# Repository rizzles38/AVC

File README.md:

# Rover 12

An autonomous 1/10th scale R/C car built by Maria Pikusova and Bob Somers.

## Documentation

### Nodes

* `joint_state_publisher` (joint\_state\_publisher/joint\_state\_publisher):
  Listens on individual joint topics under `/joints` and  publishes a single
  sensor\_msgs/JointState which contains the state of all joints in the robot
  (based on the URDF).
* `robot_state_publisher` (robot\_state\_publisher/state\_publisher): Listens
  to the combined joint states of the robot on `/joint_states`, runs forward
  kinematics based on the URDF, and publishes the results to the TF2 tree.
* `control_board` (rover12\_drivers/control\_board\_node): Driver node which
  talks to the control board. Subscribes to the `/control/autonomous` and
  `/control/command` topics for controlling whether we're in autonomous mode and
  what the velocity/steering command is. Publishes data and status of the wheel
  encoders on the `/wheels/data` and `/wheels/status` topics, as well as the
  status of autonomous mode (from the control board) on `/estop`.
* `sensor_board` (rover12\_drivers/sensor\_board\_node): Publishes data from the
  IMU sensor and GPS sensor, including status information from both sensors
  about their operating modes, current performance, and calibration status.
* `soft_estop` (soft\_estop/soft\_estop): Continuously publishes on the
  `/control/autonomous` topic that requests that the hardware allow the robot to
  be in autonomous mode. Can be run on a computer different than the robot to
  have remote control of autonomous mode. Stands for "software emergency stop".
* `odom_localizer` (robot\_localization/ukf\_localization\_node): Runs an
  unscented Kalman filter over the wheel odometry and IMU data to produce a
  state estimate of `base_link` in the `odom` frame. Subscribes to `/imu/data`
  and `/wheels/data` for sensor inputs and publishes its pose estimate on
  `/odom/filtered`. Also publishes the transform from the `odom` frame to the
  `base_link` frame in the TF2 tree.

### Topics

* `/control`: Namespace for talking to the control board.
  * `/autonomous` (rover12\_drivers/AutonomousMode): Controls whether the
    software wants to be in autonomous mode or not.
  * `/command` (ackermann\_msgs/AckermannDriveStamped): Contains the velocity
    and steering angle command we want the car to execute.
* `/estop` (rover12\_drivers/AutonomousMode): The current state of autonomous
  mode, according to the control board. The firmware makes the final call, based
  on whether the software and physical autonomous mode switch are engaged.
* `/gps`: Namespace for the GPS sensor.
  * `/fix` (sensor\_msgs/NavSatFix): Current GPS position estimate.
  * `/status` (rover12\_drivers/GpsStatus): Extra status information from the
    GPS sensor.
* `/imu`: Namespace for the inertial sensor.
  * `/data` (sensor\_msgs/Imu): Current inertial data and absolute orientation
    estimate from the sensor.
  * `/status` (rover12\_drivers/ImuStatus): Extra status information from the
    IMU, such as its operating mode and calibration state.
* `/joint_states` (sensor\_msgs/JointState): A combined, consistent JointState
  for all joints in the robot, based on the URDF. Published by the
  `joint_state_publisher`.
* `/joints`: Namespace for controlling individual joint states.
  * `/fl_steer` (sensor\_msgs/JointState): Steering rotation of the front left kingpin.
  * `/fr_steer` (sensor\_msgs/JointState): Steering rotation of the front right kingpin.
  * `/fl_wheel` (sensor\_msgs/JointState): Rotation of the front left wheel.
  * `/fr_wheel` (sensor\_msgs/JointState): Rotation of the front right wheel.
  * `/rl_wheel` (sensor\_msgs/JointState): Rotation of the rear left wheel.
  * `/rr_wheel` (sensor\_msgs/JointState): Rotation of the rear right wheel.
* `/odom`: Namespace for pose information in the odom frame.
  * `/filtered` (nav\_msgs/Odometry): Output pose estimate from the UKF in the
    `odom` frame.
* `/wheels`: Namespace for the quadrature wheel encoders.
  * `/data` (geometry\_msgs/TwistWithCovarianceStamped): Instantaneous forward
    speed based on averaging wheel speeds from the quadrature wheel encoders.
  * `/status` (rover12\_drivers/EncoderStatus): Extra status data from the
    wheel encoders (such as raw tick counts).

### TF2 Frames
* `odom`: World-fixed frame in which `base_link` moves smoothly over the short
  term, but accumulates drift error over the long term. The origin of this frame
  is the startup location of the robot.
  * `base_link`: Fixed to robot, parent of all other frames attached to the
    robot. Origin is at the rear axle (X forward, Y out the driver's side, Z
    up).
    * `imu`: Origin at the sensing center of the IMU, oriented according to the
      IMUs local coordinate frame.
    * `gps`: Origen at the sensing center of the GPS antenna, oriented in the
      same direction as `base_link`.
    * `body`: Origin at the approximate center of mass of the body shell,
      primarily used for drawing the robot model at a sensible location in rviz.
    * `rl_wheel`: Origin in the center of the rear left wheel. Rotates about
      its Y axis as the wheel rotates. Located half the track distance from
      `base_link` along its Y axis.
    * `rr_wheel`: Origin in the center of the rear right wheel. Rotates about
      its Y axis as the wheel rotates. Located half the track distance from
      `base_link` along its Y axis.
    * `f_axle`: Origin in the center of the front axle, oriented in the same
      way as `base_link`. The distance between this frame and `base_link` is the
      wheelbase distance along their colinear X axes.
      * `fl_kingpin`: Origin in the steering center of the front left wheel,
        located half the track distance from `f_axle` along its Y axis. Rotates
        about its Z axis.
        * `fl_wheel`: Origin in the center of the front left wheel, orientation
          accounting for the rotation of `fl_kingpin`. Rotates about its Y axis
          as the wheel rotates.
      * `fr_kingpin`: Origin in the steering center of the front right wheel,
        located half the track distance from `f_axle` along its Y axis. Rotates
        about its Z axis.
        * `fr_wheel`: Origin in the center of the front right wheel, orientation
          accounting for the rotation of `fr_kingpin`. Rotates about its Y axis
          as the wheel rotates.

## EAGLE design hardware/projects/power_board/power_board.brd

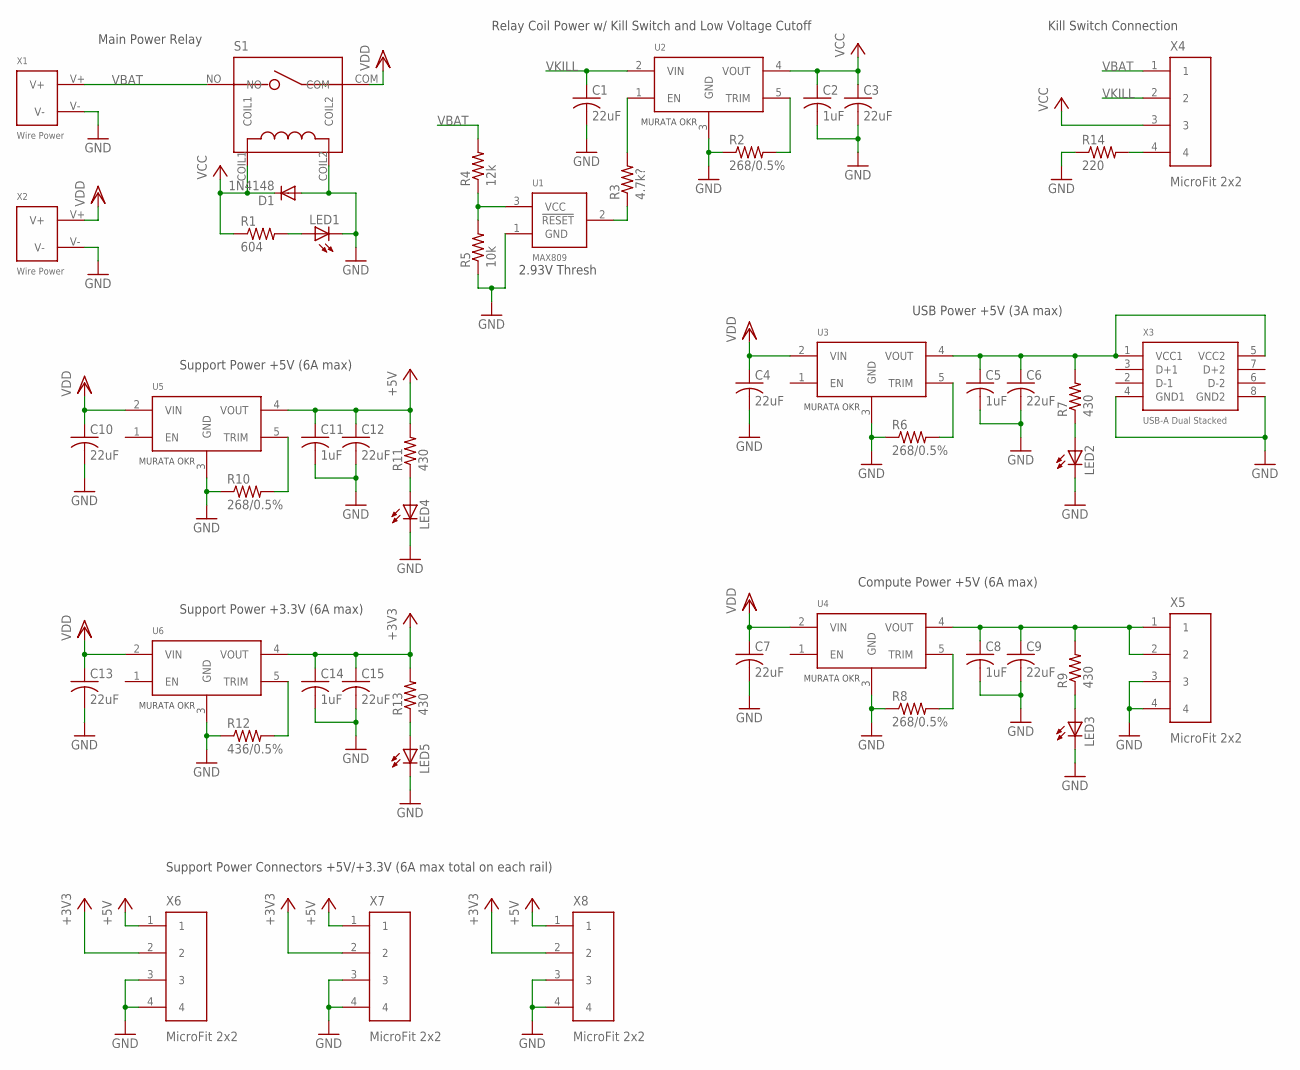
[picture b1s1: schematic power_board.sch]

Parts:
C1, C3, C4, C6, C7, C9, C10, C12, C13, C15: 22uF; C1210
C2, C5, C8, C11, C14: 1uF; C1210
D1: 1N4148; SOD123
LED1, LED2, LED3, LED4, LED5: LEDCHIPLED_0603; CHIPLED_0603
R1: 604; R0603
R2, R6, R8, R10: 268/0.5%; R0603
R3: 4.7k?; R0603
R4: 12k; R0603
R5: 10k; R0603
R7, R9, R11, R13: 430; R0603
R12: 436/0.5%; R0603
R14: 220; R0603
S1: T90S1D12-5
U1: MAX809; SOT-23
U2, U3, U4, U5, U6: MURATA-OKR
X1, X2: WIRE-POWER
X3: USB-A-STACKED
X4, X5, X6, X7, X8: MICROFIT-2X2-SMD; MICROFIT-2X2-0430450411

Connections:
+3V3: C14.1, C15.1, R13.2, U6.4 (VOUT), X6.2, X7.2, X8.2
+5V: C11.1, C12.1, R11.2, U5.4 (VOUT), X6.1, X7.1, X8.1
GND: C1.2, C2.2, C3.2, C4.2, C5.2, C6.2, C7.2, C8.2, C9.2, C10.2, C11.2, C12.2, C13.2, C14.2, C15.2, D1.A, LED1.C, LED2.C, LED3.C, LED4.C, LED5.C, R2.1, R5.1, R6.1, R8.1, R10.1, R12.1, R14.1, S1.COIL2, U1.1 (GND), U2.3 (GND), U3.3 (GND), U4.3 (GND), U5.3 (GND), U6.3 (GND), X1.V-, X2.V-, X3.4 (GND1), X3.8 (GND2), X5.3, X5.4, X6.3, X6.4, X7.3, X7.4, X8.3, X8.4
unnamed: LED2.A, R7.1
unnamed: LED1.A, R1.2
unnamed: R2.2, U2.5 (TRIM)
unnamed: R3.1, U1.2 (!RESET!)
unnamed: R8.2, U4.5 (TRIM)
unnamed: R6.2, U3.5 (TRIM)
unnamed: R4.1, R5.2, U1.3 (VCC)
unnamed: C8.1, C9.1, R9.2, U4.4 (VOUT), X5.1, X5.2
unnamed: LED3.A, R9.1
unnamed: LED4.A, R11.1
unnamed: LED5.A, R13.1
unnamed: R3.2, U2.1 (EN)
unnamed: R12.2, U6.5 (TRIM)
unnamed: R10.2, U5.5 (TRIM)
unnamed: R14.2, X4.4
USB5V: C5.1, C6.1, R7.2, U3.4 (VOUT), X3.1 (VCC1), X3.5 (VCC2)
VBAT: R4.2, S1.NO, X1.V+, X4.1
VCC: C2.1, C3.1, D1.C, R1.1, S1.COIL1, U2.4 (VOUT), X4.3
VDD: C4.1, C7.1, C10.1, C13.1, S1.COM, U3.2 (VIN), U4.2 (VIN), U5.2 (VIN), U6.2 (VIN), X2.V+
VKILL: C1.1, U2.2 (VIN), X4.2

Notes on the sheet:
Main Power Relay
Relay Coil Power w/ Kill Switch and Low Voltage Cutoff
Kill Switch Connection
USB Power +5V (3A max)
Compute Power +5V (6A max)
Support Power +5V (6A max)
Support Power +3.3V (6A max)
Support Power Connectors +5V/+3.3V (6A max total on each rail)
2.93V Thresh

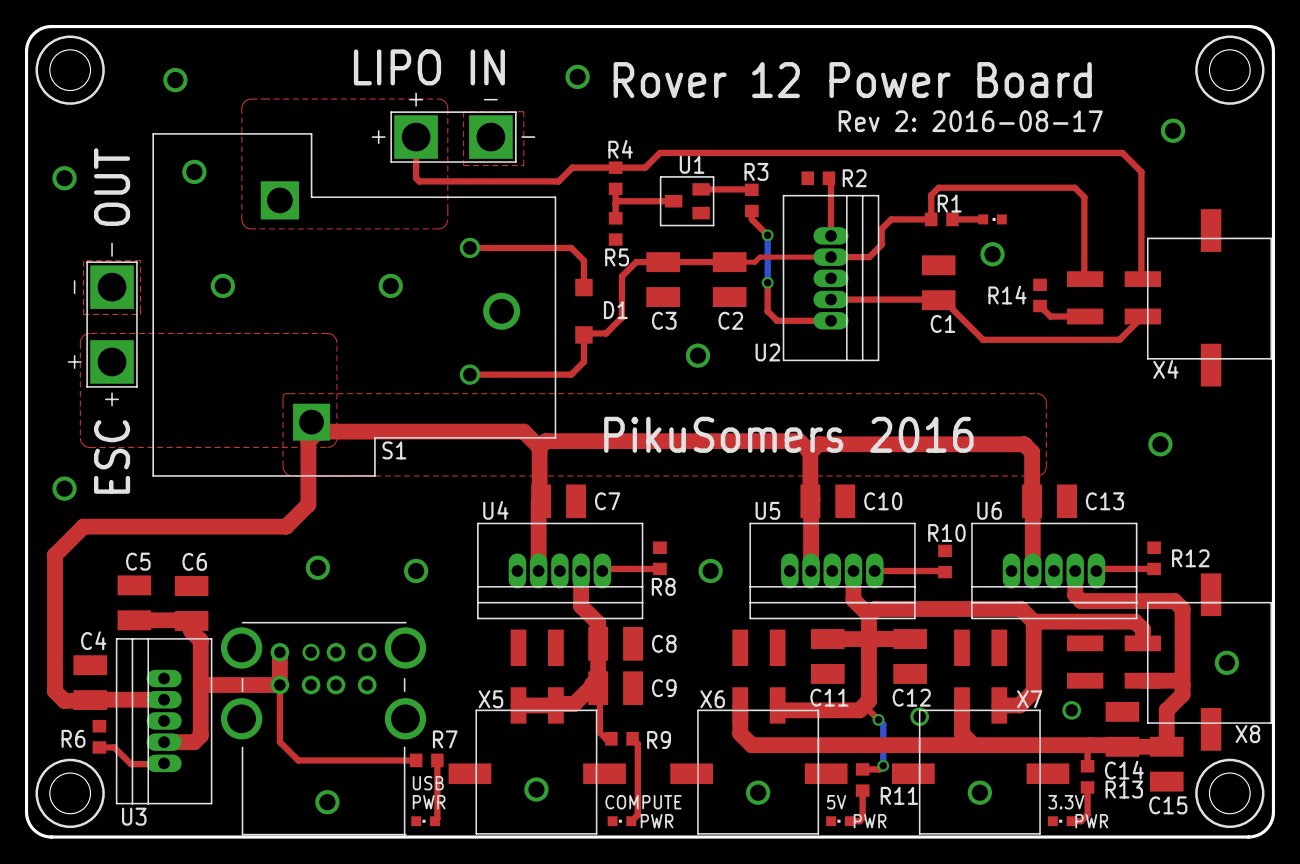
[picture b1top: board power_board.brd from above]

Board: 2 copper layers, 100.0 x 65.0 mm, 50 parts (0 on the bottom side), 23 nets.

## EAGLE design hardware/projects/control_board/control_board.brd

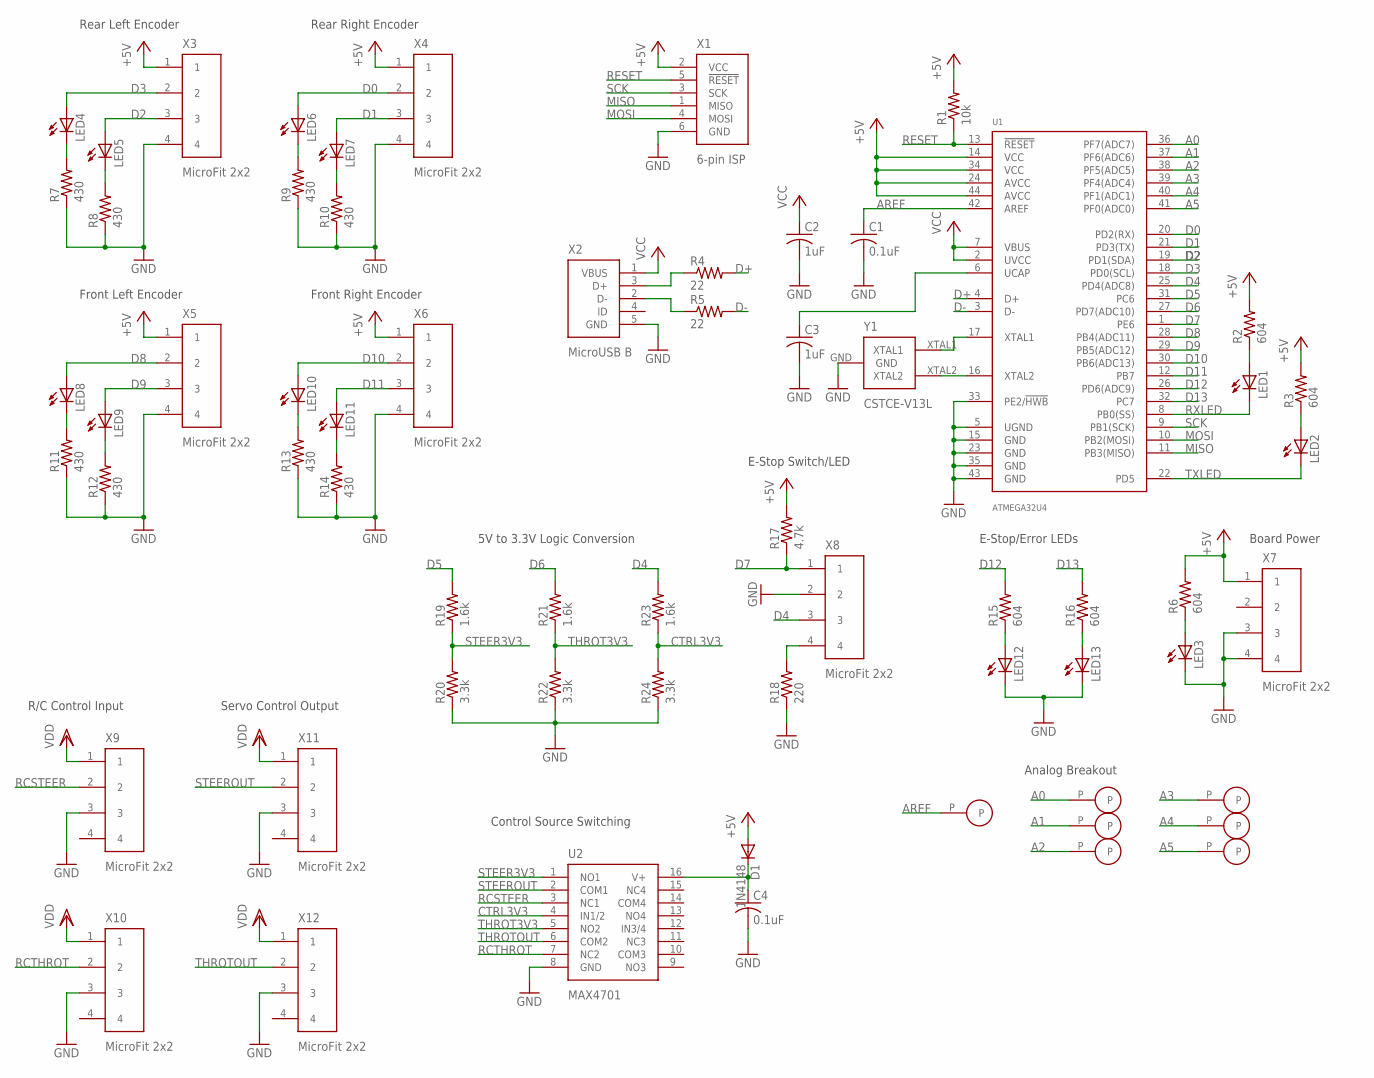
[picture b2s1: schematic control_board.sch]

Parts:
C1, C4: 0.1uF; C0603
C2, C3: 1uF; C0603
D1: 1N4148; SOD123
LED1, LED2, LED3, LED4, LED5, LED6, LED7, LED8, LED9, LED10, LED11, LED12, LED13: LEDCHIPLED_0603; CHIPLED_0603
P1, P2, P3, P4, P5, P6, P7: 100MIL-PAD
R1: 10k; R0603
R2, R3, R6, R15, R16: 604; R0603
R4, R5: 22; R0603
R7, R8, R9, R10, R11, R12, R13, R14: 430; R0603
R17: 4.7k; R0603
R18: 220; R0603
R19, R21, R23: 1.6k; R0603
R20, R22, R24: 3.3k; R0603
U1: ATMEGA32U4; TQFP-44
U2: MAX4701; TSSOP-16
X1: ISP-HEADER
X2: MICRO-USB-B
X3, X4, X5, X6, X7, X8, X9, X10, X11, X12: MICROFIT-2X2-SMD; MICROFIT-2X2-0430450411
Y1: CSTCE-V13L

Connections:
+5V: D1.A, R1.2, R2.2, R3.2, R6.2, R17.2, U1.14 (VCC), U1.24 (AVCC), U1.34 (VCC), U1.44 (AVCC), X1.2 (VCC), X3.1, X4.1, X5.1, X6.1, X7.1
A0: P2.P, U1.36 (PF7(ADC7))
A1: P3.P, U1.37 (PF6(ADC6))
A2: P4.P, U1.38 (PF5(ADC5))
A3: P5.P, U1.39 (PF4(ADC4))
A4: P6.P, U1.40 (PF1(ADC1))
A5: P7.P, U1.41 (PF0(ADC0))
AREF: C1.1, P1.P, U1.42 (AREF)
CTRL3V3: R23.1, R24.2, U2.4 (IN1/2)
D0: LED6.A, U1.20 (PD2(RX)), X4.2
D1: LED7.A, U1.21 (PD3(TX)), X4.3
D2: LED5.A, U1.19 (PD1(SDA)), X3.3
D3: LED4.A, U1.18 (PD0(SCL)), X3.2
D4: R23.2, U1.25 (PD4(ADC8)), X8.3
D5: R19.2, U1.31 (PC6)
D6: R21.2, U1.27 (PD7(ADC10))
D7: R17.1, U1.1 (PE6), X8.1
D8: LED8.A, U1.28 (PB4(ADC11)), X5.2
D9: LED9.A, U1.29 (PB5(ADC12)), X5.3
D10: LED10.A, U1.30 (PB6(ADC13)), X6.2
D11: LED11.A, U1.12 (PB7), X6.3
D12: R15.2, U1.26 (PD6(ADC9))
D13: R16.2, U1.32 (PC7)
D+: R4.2, U1.4 (D+)
D-: R5.2, U1.3 (D-)
GND: C1.2, C2.2, C3.2, C4.2, LED3.C, LED12.C, LED13.C, R7.1, R8.1, R9.1, R10.1, R11.1, R12.1, R13.1, R14.1, R18.1, R20.1, R22.1, R24.1, U1.5 (UGND), U1.15 (GND), U1.23 (GND), U1.33 (PE2/!HWB!), U1.35 (GND), U1.43 (GND), U2.8 (GND), X1.6 (GND), X2.5 (GND), X3.4, X4.4, X5.4, X6.4, X7.3, X7.4, X8.2, X9.3, X10.3, X11.3, X12.3, Y1.GND
MISO: U1.11 (PB3(MISO)), X1.1 (MISO)
MOSI: U1.10 (PB2(MOSI)), X1.4 (MOSI)
unnamed: LED3.A, R6.1
unnamed: C3.1, U1.6 (UCAP)
unnamed: LED1.A, R2.1
unnamed: LED2.A, R3.1
unnamed: U1.16 (XTAL2), Y1.XTAL2
unnamed: U1.17 (XTAL1), Y1.XTAL1
unnamed: LED7.C, R10.2
unnamed: R5.1, X2.2 (D-)
unnamed: R4.1, X2.3 (D+)
unnamed: LED4.C, R7.2
unnamed: LED6.C, R9.2
unnamed: LED5.C, R8.2
unnamed: LED8.C, R11.2
unnamed: LED9.C, R12.2
unnamed: LED12.A, R15.1
unnamed: LED13.A, R16.1
unnamed: R18.2, X8.4
unnamed: LED10.C, R13.2
unnamed: LED11.C, R14.2
unnamed: C4.1, D1.C, U2.16 (V+)
RCSTEER: U2.3 (NC1), X9.2
RCTHROT: U2.7 (NC2), X10.2
RESET: R1.1, U1.13 (!RESET!), X1.5 (!RESET!)
RXLED: LED1.C, U1.8 (PB0(SS))
SCK: U1.9 (PB1(SCK)), X1.3 (SCK)
STEER3V3: R19.1, R20.2, U2.1 (NO1)
STEEROUT: U2.2 (COM1), X11.2
THROT3V3: R21.1, R22.2, U2.5 (NO2)
THROTOUT: U2.6 (COM2), X12.2
TXLED: LED2.C, U1.22 (PD5)
VCC: C2.1, U1.2 (UVCC), U1.7 (VBUS), X2.1 (VBUS)
VDD: X9.1, X10.1, X11.1, X12.1

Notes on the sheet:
Rear Left Encoder
Rear Right Encoder
Front Left Encoder
Front Right Encoder
Board Power
E-Stop/Error LEDs
E-Stop Switch/LED
R/C Control Input
Servo Control Output
Control Source Switching
5V to 3.3V Logic Conversion
Analog Breakout

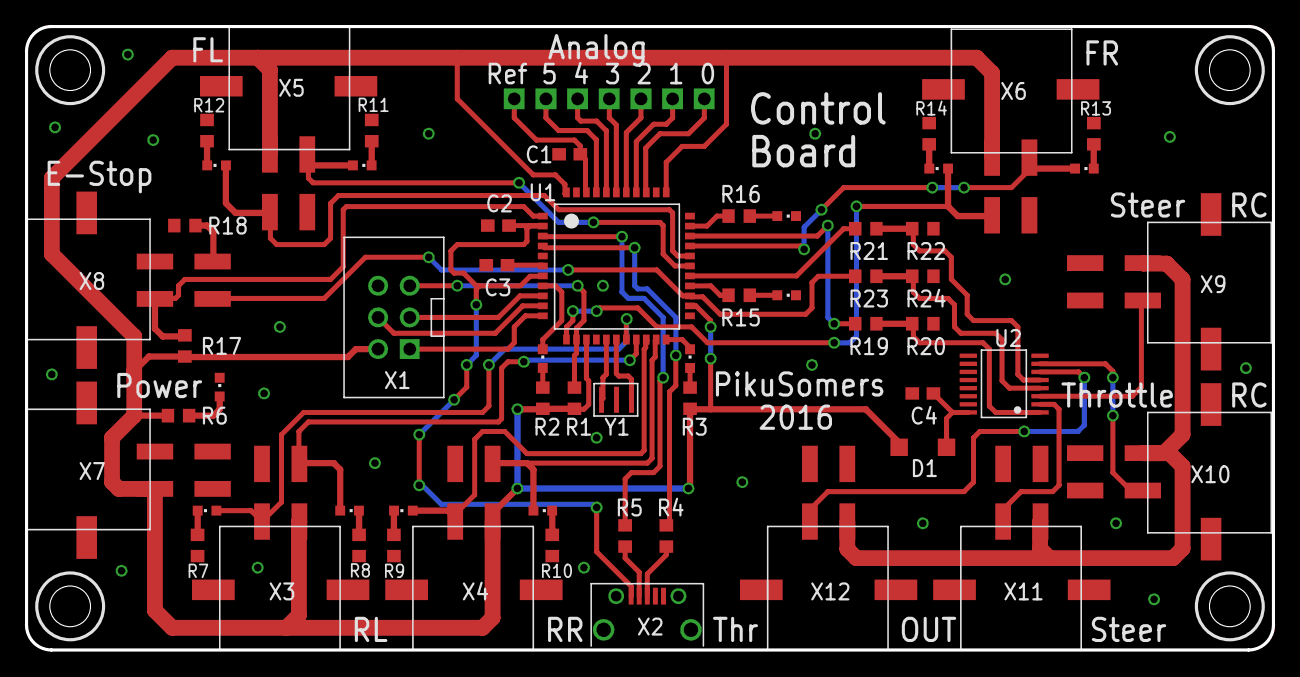
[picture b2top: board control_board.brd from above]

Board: 2 copper layers, 100.0 x 50.0 mm, 64 parts (0 on the bottom side), 60 nets.

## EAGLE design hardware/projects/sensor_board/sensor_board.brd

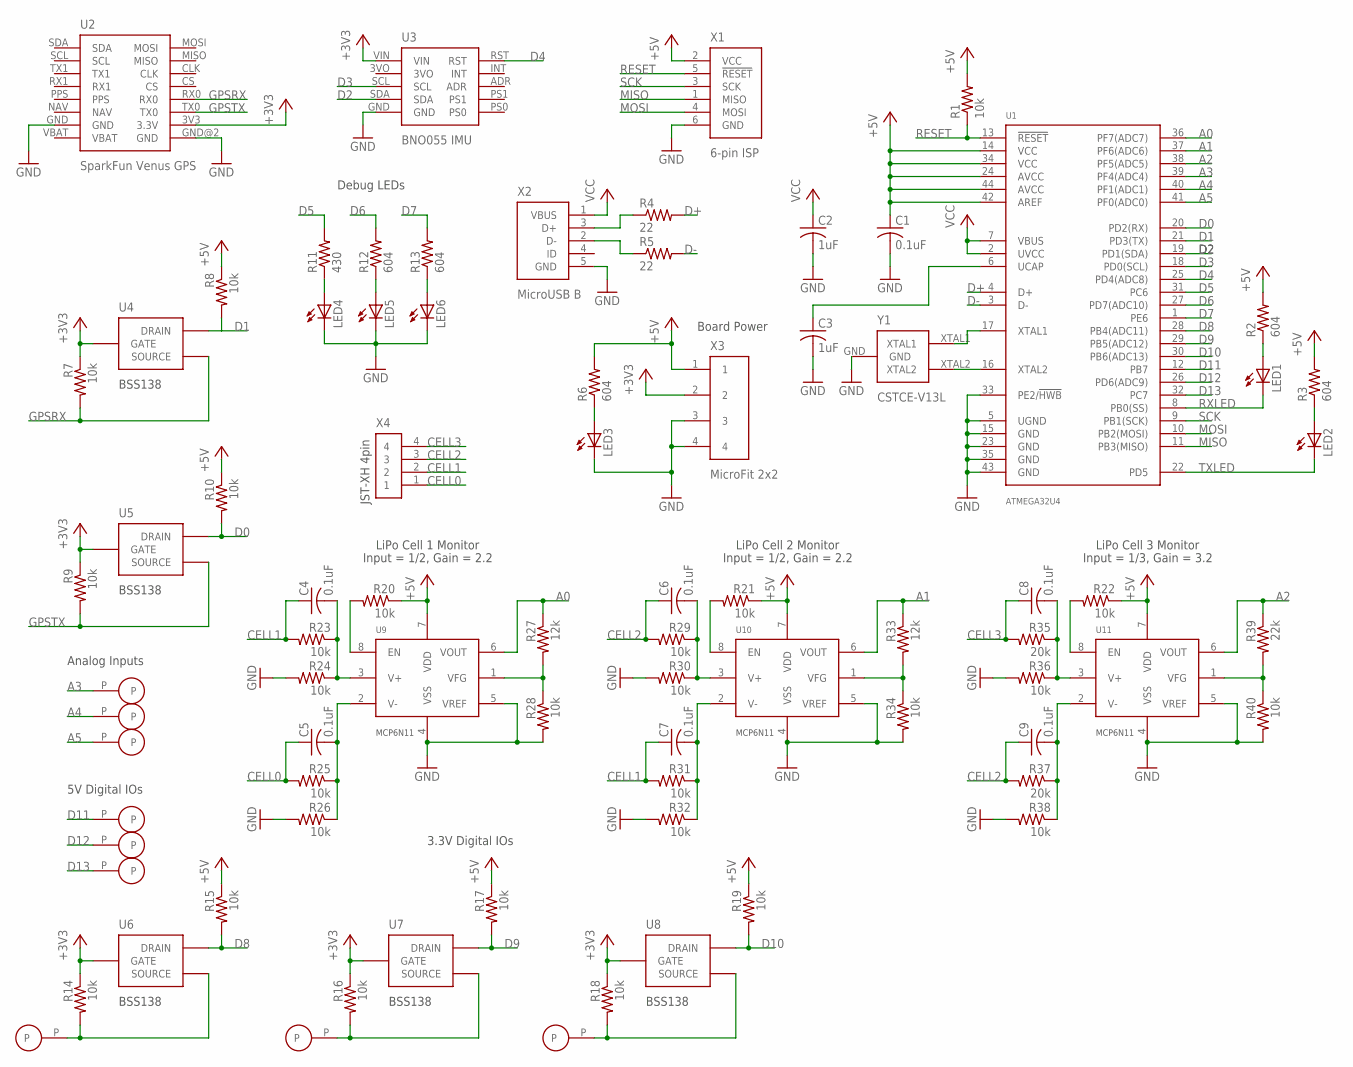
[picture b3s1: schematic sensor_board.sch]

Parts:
C1, C4, C5, C6, C7, C8, C9: 0.1uF; C0603
C2, C3: 1uF; C0603
LED1, LED2, LED3, LED4, LED5, LED6: LEDCHIPLED_0603; CHIPLED_0603
P1, P2, P3, P4, P5, P6, P8, P9, P10: 100MIL-PAD
R1, R7, R8, R9, R10, R14, R15, R16, R17, R18, R19, R20, R21, R22, R23, R24, R25, R26, R28, R29, R30, R31, R32, R34, R36, R38, R40: 10k; R0603
R2, R3, R6, R12, R13: 604; R0603
R4, R5: 22; R0603
R11: 430; R0603
R27, R33: 12k; R0603
R35, R37: 20k; R0603
R39: 22k; R0603
U1: ATMEGA32U4; TQFP-44
U2: SPARKFUN-VENUS-GPS
U3: ADAFRUIT-BNO055-IMU
U4, U5, U6, U7, U8: BSS138; SOT-23
U9, U10, U11: MCP6N11; SOIC-8
X1: ISP-HEADER
X2: MICRO-USB-B
X3: MICROFIT-2X2-SMD; MICROFIT-2X2-0430450411
X4: JST-XH-4
Y1: CSTCE-V13L

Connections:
3V3D8: P4.P, R14.2, U6.SOURCE
3V3D9: P5.P, R16.2, U7.SOURCE
3V3D10: P6.P, R18.2, U8.SOURCE
3VO: U3.3VO
+3V3: R7.1, R9.1, R14.1, R16.1, R18.1, U2.3V3 (3.3V), U3.VIN, U4.GATE, U5.GATE, U6.GATE, U7.GATE, U8.GATE, X3.2
+5V: C1.1, R1.2, R2.2, R3.2, R6.2, R8.1, R10.1, R15.1, R17.1, R19.1, R20.1, R21.1, R22.1, U1.14 (VCC), U1.24 (AVCC), U1.34 (VCC), U1.42 (AREF), U1.44 (AVCC), U9.7 (VDD), U10.7 (VDD), U11.7 (VDD), X1.2 (VCC), X3.1
A0: R27.1, U1.36 (PF7(ADC7)), U9.6 (VOUT)
A1: R33.1, U1.37 (PF6(ADC6)), U10.6 (VOUT)
A2: R39.1, U1.38 (PF5(ADC5)), U11.6 (VOUT)
A3: P8.P, U1.39 (PF4(ADC4))
A4: P9.P, U1.40 (PF1(ADC1))
A5: P10.P, U1.41 (PF0(ADC0))
CELL0: C5.1, R25.2, X4.1
CELL1: C4.1, C7.1, R23.2, R31.2, X4.2
CELL2: C6.1, C9.1, R29.2, R37.2, X4.3
CELL3: C8.1, R35.2, X4.4
D0: R10.2, U1.20 (PD2(RX)), U5.DRAIN
D1: R8.2, U1.21 (PD3(TX)), U4.DRAIN
D2: U1.19 (PD1(SDA)), U3.SDA
D3: U1.18 (PD0(SCL)), U3.SCL
D4: U1.25 (PD4(ADC8)), U3.RST
D5: R11.2, U1.31 (PC6)
D6: R12.2, U1.27 (PD7(ADC10))
D7: R13.2, U1.1 (PE6)
D8: R15.2, U1.28 (PB4(ADC11)), U6.DRAIN
D9: R17.2, U1.29 (PB5(ADC12)), U7.DRAIN
D10: R19.2, U1.30 (PB6(ADC13)), U8.DRAIN
D11: P1.P, U1.12 (PB7)
D12: P2.P, U1.26 (PD6(ADC9))
D13: P3.P, U1.32 (PC7)
D+: R4.2, U1.4 (D+)
D-: R5.2, U1.3 (D-)
GND: C1.2, C2.2, C3.2, LED3.C, LED4.C, LED5.C, LED6.C, R24.2, R26.2, R28.2, R30.2, R32.2, R34.2, R36.2, R38.2, R40.2, U1.5 (UGND), U1.15 (GND), U1.23 (GND), U1.33 (PE2/!HWB!), U1.35 (GND), U1.43 (GND), U2.GND, U2.GND@2 (GND), U3.GND, U9.4 (VSS), U9.5 (VREF), U10.4 (VSS), U10.5 (VREF), U11.4 (VSS), U11.5 (VREF), X1.6 (GND), X2.5 (GND), X3.3, X3.4, Y1.GND
GPSRX: R7.2, U2.RX0, U4.SOURCE
GPSTX: R9.2, U2.TX0, U5.SOURCE
MISO: U1.11 (PB3(MISO)), X1.1 (MISO)
MOSI: U1.10 (PB2(MOSI)), X1.4 (MOSI)
unnamed: LED3.A, R6.1
unnamed: C3.1, U1.6 (UCAP)
unnamed: LED1.A, R2.1
unnamed: LED2.A, R3.1
unnamed: U1.16 (XTAL2), Y1.XTAL2
unnamed: U1.17 (XTAL1), Y1.XTAL1
unnamed: R20.2, U9.8 (EN)
unnamed: R5.1, X2.2 (D-)
unnamed: R4.1, X2.3 (D+)
unnamed: LED4.A, R11.1
unnamed: LED5.A, R12.1
unnamed: LED6.A, R13.1
unnamed: R21.2, U10.8 (EN)
unnamed: R22.2, U11.8 (EN)
unnamed: C4.2, R23.1, R24.1, U9.3 (V+)
unnamed: C8.2, R35.1, R36.1, U11.3 (V+)
unnamed: C5.2, R25.1, R26.1, U9.2 (V-)
unnamed: C6.2, R29.1, R30.1, U10.3 (V+)
unnamed: R27.2, R28.1, U9.1 (VFG)
unnamed: C7.2, R31.1, R32.1, U10.2 (V-)
unnamed: C9.2, R37.1, R38.1, U11.2 (V-)
unnamed: R33.2, R34.1, U10.1 (VFG)
unnamed: R39.2, R40.1, U11.1 (VFG)
RESET: R1.1, U1.13 (!RESET!), X1.5 (!RESET!)
RXLED: LED1.C, U1.8 (PB0(SS))
SCK: U1.9 (PB1(SCK)), X1.3 (SCK)
TXLED: LED2.C, U1.22 (PD5)
VBAT: U2.VBAT
VCC: C2.1, U1.2 (UVCC), U1.7 (VBUS), X2.1 (VBUS)

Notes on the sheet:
Board Power
Debug LEDs
3.3V Digital IOs
5V Digital IOs
Analog Inputs
LiPo Cell 1 Monitor
LiPo Cell 2 Monitor
LiPo Cell 3 Monitor
Input = 1/2, Gain = 2.2
Input = 1/3, Gain = 3.2

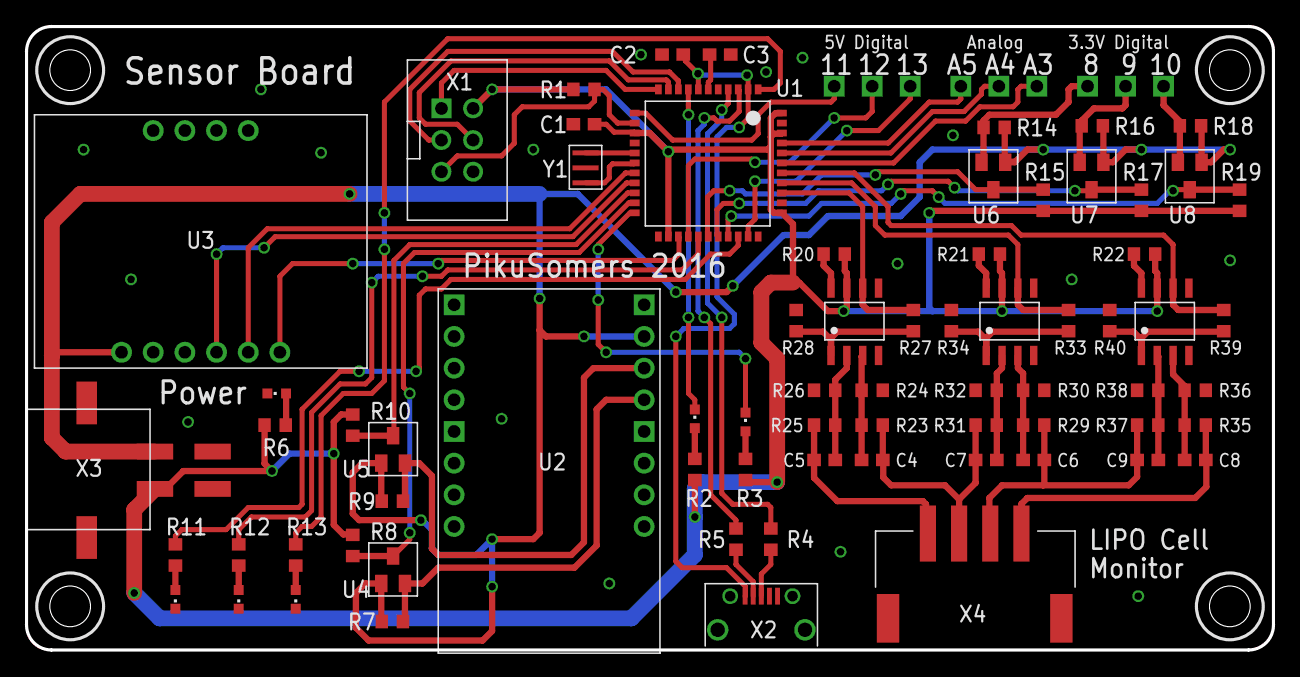
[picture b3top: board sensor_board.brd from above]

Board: 2 copper layers, 100.0 x 50.0 mm, 80 parts (0 on the bottom side), 64 nets.

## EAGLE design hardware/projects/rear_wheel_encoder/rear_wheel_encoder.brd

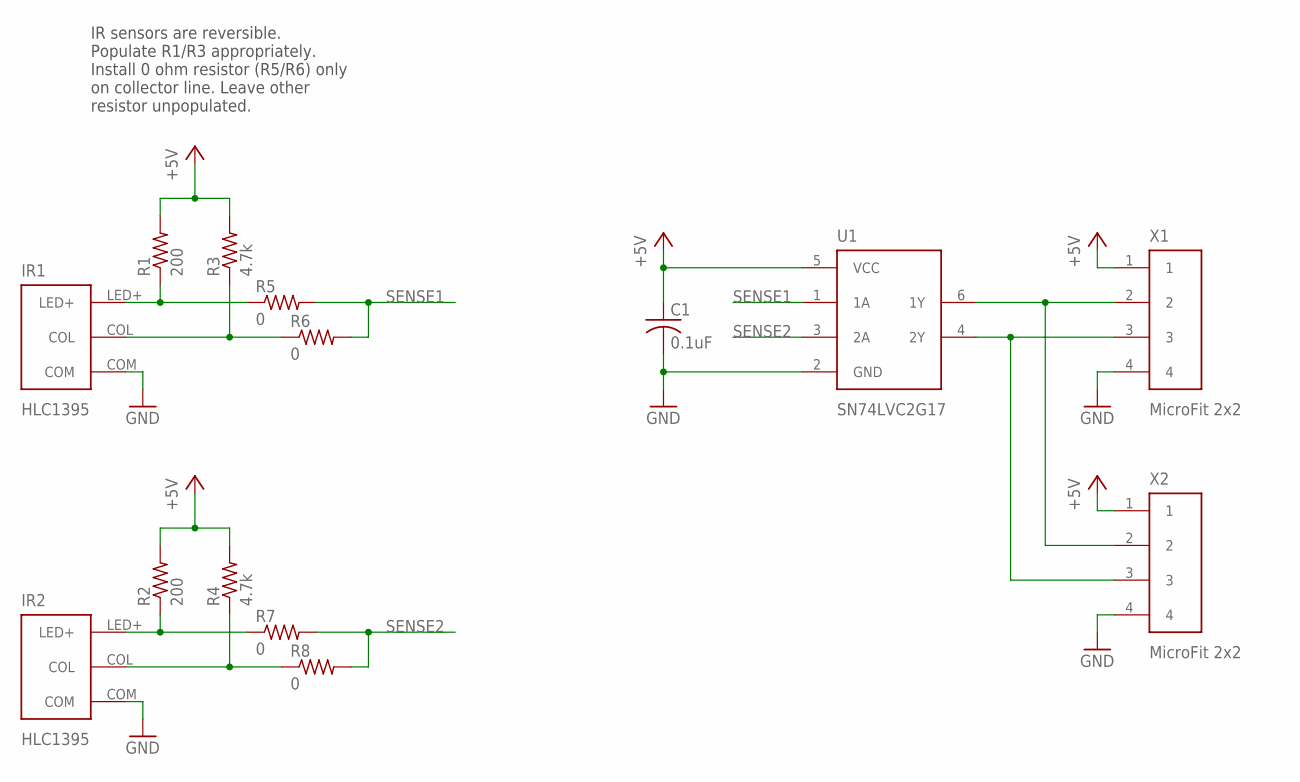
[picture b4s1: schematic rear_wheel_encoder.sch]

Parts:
C1: 0.1uF; C0603
IR1, IR2: HLC1395
R1, R2: 200; R0603
R3, R4: 4.7k; R0603
R5, R6, R7, R8: 0; R0603
U1: SN74LVC2G17DBVR; SOT-23-6
X1, X2: MICROFIT-2X2-SMD; MICROFIT-2X2-0430450411

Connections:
+5V: C1.1, R1.2, R2.2, R3.2, R4.2, U1.5 (VCC), X1.1, X2.1
GND: C1.2, IR1.COM, IR2.COM, U1.2 (GND), X1.4, X2.4
unnamed: IR1.LED+, R1.1, R5.1
unnamed: IR2.LED+, R2.1, R7.1
unnamed: IR2.COL, R4.1, R8.1
unnamed: U1.4 (2Y), X1.3, X2.3
unnamed: U1.6 (1Y), X1.2, X2.2
unnamed: IR1.COL, R3.1, R6.1
SENSE1: R5.2, R6.2, U1.1 (1A)
SENSE2: R7.2, R8.2, U1.3 (2A)

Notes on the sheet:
IR sensors are reversible. Populate R1/R3 appropriately. Install 0 ohm resistor (R5/R6) only on collector line. Leave other resistor unpopulated.

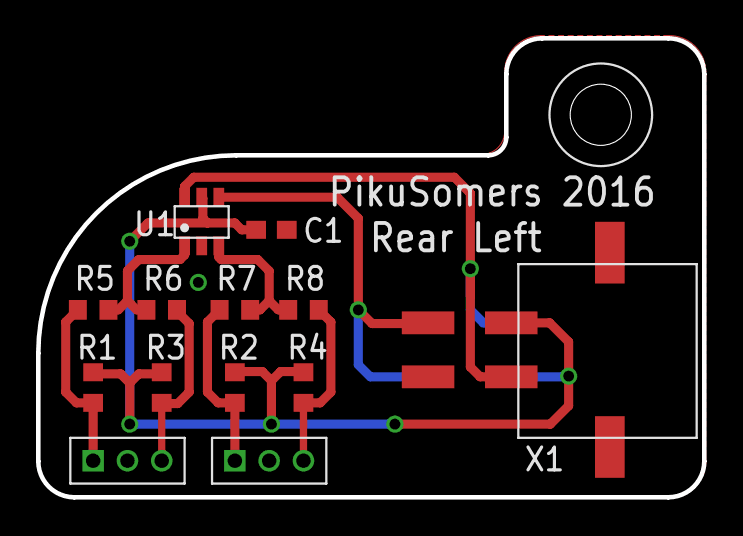
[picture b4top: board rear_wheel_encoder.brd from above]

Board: 2 copper layers, 37.0 x 25.5 mm, 14 parts (1 on the bottom side), 10 nets.

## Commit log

2016-07-10 Initial workspace commit.
2016-07-12 Importing urg_c library from Indigo.
2016-07-12 Fix sample bugs.
2016-07-12 Import laser_proc and urg_node packages. They seem to compile.
2016-07-19 Adding EAGLE library and empty project for wheel encoder boards.
2016-07-20 Added MicroFit 2x2 to library and wheel sensor schematic.
2016-07-23 Hardware updates.
2016-07-24 Moar work.
2016-07-24 More work.
2016-07-24 Yep, more work.
2016-07-24 Getting close on control board.
2016-07-24 Getting really close!
2016-07-25 Control board schematic/BOM done!
2016-07-25 Adding sensor board.
2016-07-25 Added SparkFun Venus symbol.
2016-07-25 GPS and IMU symbols.
2016-07-27 Sensor board almost done. Needs extra I/Os broken out.
2016-07-29 Add the rover12_description package.
    Added a URDF to describe the coordinate frames of our robot, with some
    visual models for the body and wheels. The rear and front wheels can
    rotate and the front wheels can steer.
    This also adds some useful launch files for visualizing the URDF and
    loading the robot configuration (launch/rover12.launch).
    The configuration of the joint_state_publisher and
2016-07-29 Added rover12_msgs package and simulator package.
2016-07-29 Simulator node up and running.
2016-07-29 Basic launch file and config.
2016-07-29 Broadcaster node which publishes odometry to tf tree.
2016-07-29 Simulator publishing fake odometry.
2016-07-30 Added AREF breakout to control board.
2016-07-30 Finished sensor board schematic.
2016-07-31 Added LiPo cell monitors to sensor board.
2016-07-31 Added power board schematic.
2016-07-31 All parts for power board.
2016-08-01 Power board nearly done.
2016-08-01 Done with power board schematic.
2016-08-01 Fixup notes.
2016-08-01 Fixups.
2016-08-01 Ordered test fit parts.
2016-08-02 Osh Park design rules and mirrored wheel encoders.
2016-08-03 Test fitting parts. Rear wheel encoder mostly done.
2016-08-04 Renaming wheel_encoder to rear_wheel_encoder.
2016-08-04 Adding front_wheel_encoder as a copy of rear_wheel_encoder.
2016-08-04 Front wheel encoder mostly done, fixed schematic error in both encoders.
2016-08-04 Front wheel encoder passes OshPark's DRC.
2016-08-05 Rear wheel encoder done and passes OshPark DRC.
2016-08-05 Use vector fonts for board silkscreen.
2016-08-05 Screw head outlines.
2016-08-08 Power board routed.
2016-08-08 Minor silk adjustment.
2016-08-08 More minor silk adjustments.
2016-08-10 Control board getting close.
2016-08-11 Finished routing control board.
2016-08-11 Fix hole size in control board, placment work on sensor board.
2016-08-12 Routing work on sensor board.
2016-08-12 Sensor board nearly complete.
2016-08-12 Sensor board routed.
2016-08-13 Minor fixups to sensor board.
2016-08-13 Work in progress.
2016-08-13 Adding PCC library package.
2016-08-14 Fleshing things out.
2016-08-14 Added simple conversion function to nav_msgs::Path.
2016-08-14 Just construct the curve with the control points for now.
2016-08-17 Power board fixes for airwires, thermals, Murata pads.
2016-08-17 Added inline resistor for reset monitor and rev 2 silk.
2016-08-21 Adding firmware directory.
2016-08-21 Quadrature encoder pattern generator.
2016-08-21 Sized the encoder strip.
2016-08-22 Fix airwire in front wheel encoder.
2016-08-23 Adding some files for serial communication with our custom hardware.
2016-08-23 Going with 20 stripes on the quadrature pattern.
2016-08-31 Notes on ROS source install tweaking and empty so far udev rules.
2016-09-01 Serial message framing.
2016-09-01 Setting things up. Time for crc32(), cobs(), and uncobs().
2016-09-02 CRC32 checksum, COBS, and unCOBS working!
2016-09-05 Basic OpenGL 3.3 app.
2016-09-05 Window WIP.
2016-09-10 Getting sensor board firmware up and running.
2016-09-10 More sensor board firmware.
2016-09-10 More libraries.
2016-09-11 Reading rear quadrature encoders
2016-09-11 Fixed wheel encoder bug.
2016-09-11 Sensor board nearly done for now.
2016-09-11 Get rover12_comm compiling on both sides of the cable.
2016-09-11 Fix COBS bug.
2016-09-11 Added steering calibration logic
2016-09-11 Messenger and fixed COBS. No transmission failures!
2016-09-11 Print IMU messages.
2016-09-11 Datasheet for BNO055.
2016-09-11 Update IMU message and data rate.
2016-09-11 Doh, float = double on AVR.
2016-09-11 Seperate IMU calibration into ImuCal message.
2016-09-11 Break IMU data and calibration into two separate messages.
2016-09-11 Increased throttle for steering calibration
2016-09-11 Basic GPS decoding.
2016-09-11 Separate IMU cal message in firmware.
2016-09-11 Add GPS passthru sketch.
2016-09-11 Disable position pinning on the Venus.
2016-09-11 Publish GPS data and status.
2016-09-12 Maria was right. I was wrong.
2016-09-12 Added messages with wheel encoder counts
2016-09-12 Unified firmware.
2016-09-12 Wheel encoders!
2016-09-12 Publishing wheel encoder data!
2016-09-12 Future note to self.
2016-09-12 Adding vehicle computer config files.
2016-09-12 Added a script for mapping steering angle to servo commands
2016-09-13 Updated URDF with GPS and IMU frames.
2016-09-13 Lauch file package and initial sensor covariances.
2016-09-13 Remote rviz launch scripts.
2016-09-13 Only set covariance in ctor.
2016-09-13 Control board node sends control and autonomous message.
2016-09-13 OMG IT WORKS KINDA.
2016-09-13 Update remote rviz config.
2016-09-13 Fix my screw up.
2016-09-13 Actually add FastGPIO not as a submodule *facepalm*.
2016-09-13 In case we need to reset the Venus again...
2016-09-13 Software emergency stop.
2016-09-13 Launch files incorporating software estop.
2016-09-13 Remove unused include directory.
2016-09-13 Add navsat_transform and map frame localizer.
2016-09-14 Updated remote rviz.
2016-09-14 Tweaked a bunch of things. Smooth odom localization it is. GPS sucks.
2016-09-14 PID gains set from ROS params.
2016-09-14 Added PI control loop for velocity
2016-09-14 Fix awful non-blocking bug in serial comm.
2016-09-14 Send PID gains a couple times to make them stick.
2016-09-14 Control firmware... done?
2016-09-14 Saving progress on control firmware.
2016-09-14 Velocity impulse tool for PID tuning.
2016-09-14 Build a hacky Path message for the planner/display from Odometry logs.
2016-09-14 Use velocity scaling.
2016-09-16 Planner infrastructure.
2016-09-16 Ready to go except for heading error term.
2016-09-23 My serial port code is garbage. William's is better.
2016-09-23 Rename launch files, remove localizer from it.
2016-09-24 Firmware fixes and debugging.
2016-09-24 Changed a bit.
2016-09-24 Working on PID velocity control.
2016-12-22 Documenting tf2 frames.
2016-12-22 Added joint_state_publisher.
2016-12-22 Added robot_state_publisher.
2016-12-22 Information about driver nodes and sensor/control topics.
2016-12-22 Added localizer information.
2016-12-22 Update maintainer/author.
2017-01-02 Remove upstream packages, no longer needed.
2017-01-03 Wi-Fi network config for Ubuntu 16.04.
2017-01-09 Adding useful scripts for building ROS and useful packages from source.
2017-01-09 WIP, putting new control message spec in firmware.
2017-01-09 Minor firmware compile fix.
2017-01-18 Remove PID gains from control_board_node.
2017-01-18 Add ServoControl message.
2017-01-21 Update command message type in control_board_node.
2017-01-21 Update control board launch file to remove control gains.
2017-01-21 Do-nothing planner that loads and publishes a trajectory.
2017-02-10 Controller tuning bag file generation.
2017-02-12 Controller tuning test bags generation script.
2017-02-13 Remove debug messages from control board firmware.
2017-02-13 Don't need the velocity_impulse package anymore.
2017-02-13 Fix invalid timestamps in generated bags.
2017-02-13 Fix queue sizes.
2017-02-13 Add hardware timestamp to wheel encoders message.
2017-02-13 Publish hardware timestamp.
2017-06-30 Update firmware to report wheel encoders at 10 Hz.
2017-06-30 Compute time delta based on difference in hardware timestamp.
